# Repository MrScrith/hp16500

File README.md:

# hp16500
Project contains multiple items for the hp16500 testing mainframe.

Eventually there will be scripts, configurations, interface board designs and more as I get my HP16500 up and running and integrated into my FPGA and Embedded development workflow.

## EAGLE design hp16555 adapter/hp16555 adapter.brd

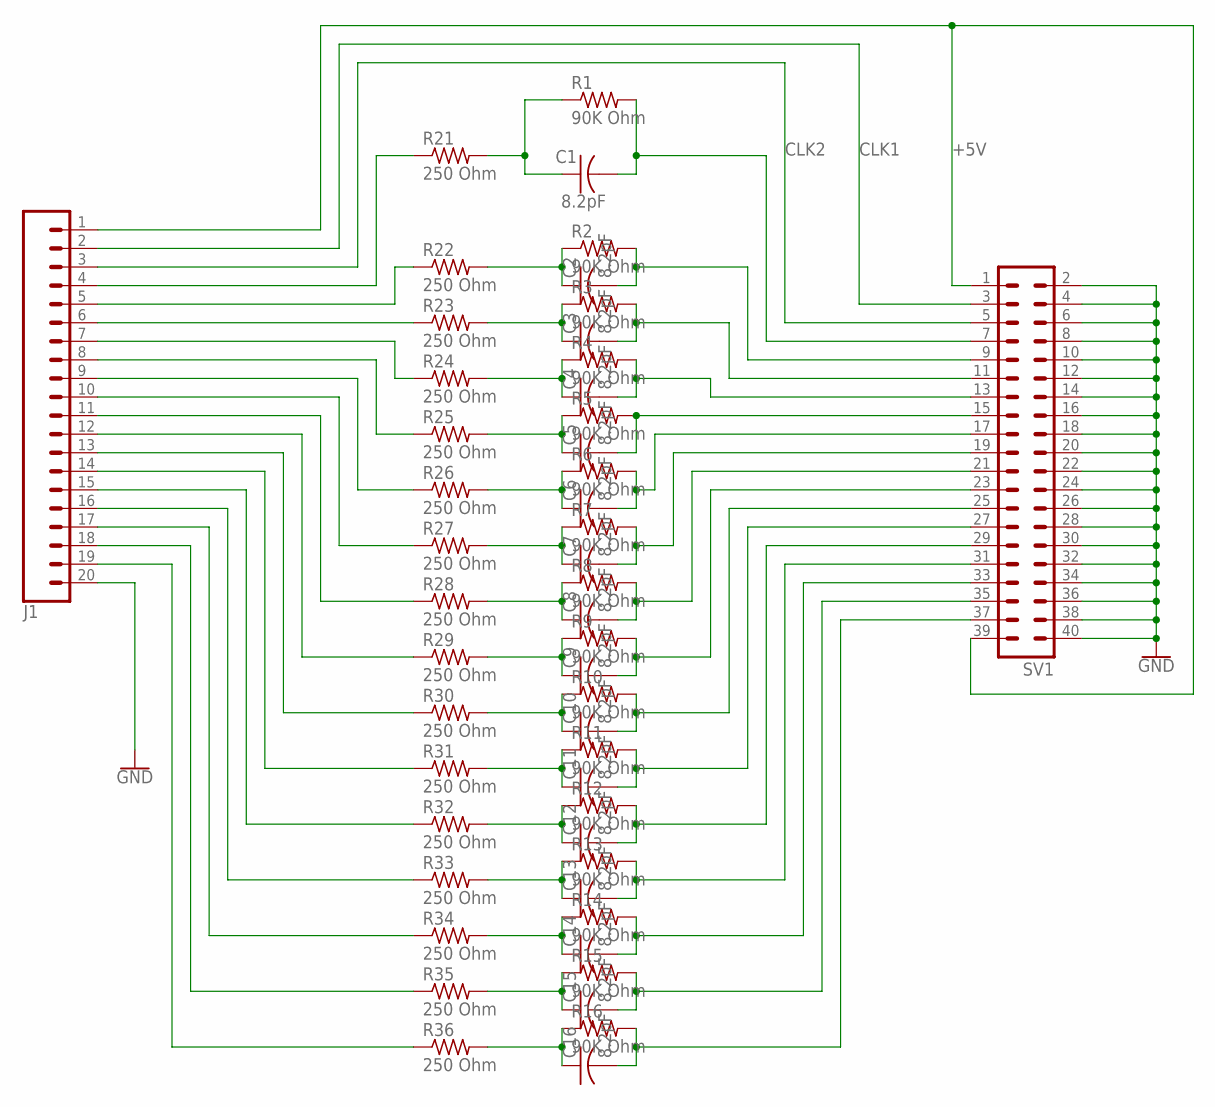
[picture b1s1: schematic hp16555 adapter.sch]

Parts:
C1, C2, C3, C4, C5, C6, C7, C8, C9, C10, C11, C12, C13, C14, C15, C16: 8.2pF; C1206
J1: CONN_20; 1X20
R1, R2, R3, R4, R5, R6, R7, R8, R9, R10, R11, R12, R13, R14, R15, R16: 90K Ohm; M1206
R21, R22, R23, R24, R25, R26, R27, R28, R29, R30, R31, R32, R33, R34, R35, R36: 250 Ohm; M1206
SV1: MA20-2

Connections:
+5V: J1.1, SV1.1, SV1.39
CLK1: J1.2, SV1.3
CLK2: J1.3, SV1.5
D0: C16.2, R16.2, SV1.37
D0-I: J1.19, R36.1
D1: C15.2, R15.2, SV1.35
D1-I: J1.18, R35.1
D2: C14.2, R14.2, SV1.33
D2-I: J1.17, R34.1
D3: C13.2, R13.2, SV1.31
D3-I: J1.16, R33.1
D4: C12.2, R12.2, SV1.29
D4-I: J1.15, R32.1
D5: C11.2, R11.2, SV1.27
D5-I: J1.14, R31.1
D6: C10.2, R10.2, SV1.25
D6-I: J1.13, R30.1
D7: C9.2, R9.2, SV1.23
D7-I: J1.12, R29.1
D8: C8.2, R8.2, SV1.21
D8-I: J1.11, R28.1
D9: C7.2, R7.2, SV1.19
D9-I: J1.10, R27.1
D10: C6.2, R6.2, SV1.17
D10-I: J1.9, R26.1
D11: C5.2, R5.2, SV1.15
D11-I: J1.8, R25.1
D12: C4.2, R4.2, SV1.13
D12-I: J1.7, R24.1
D13: C3.2, R3.2, SV1.11
D13-I: J1.6, R23.1
D14: C2.2, R2.2, SV1.9
D14-I: J1.5, R22.1
D15: C1.2, R1.2, SV1.7
D15-I: J1.4, R21.1
GND: J1.20, SV1.2, SV1.4, SV1.6, SV1.8, SV1.10, SV1.12, SV1.14, SV1.16, SV1.18, SV1.20, SV1.22, SV1.24, SV1.26, SV1.28, SV1.30, SV1.32, SV1.34, SV1.36, SV1.38, SV1.40
unnamed: C16.1, R16.1, R36.2
unnamed: C15.1, R15.1, R35.2
unnamed: C14.1, R14.1, R34.2
unnamed: C13.1, R13.1, R33.2
unnamed: C12.1, R12.1, R32.2
unnamed: C11.1, R11.1, R31.2
unnamed: C10.1, R10.1, R30.2
unnamed: C9.1, R9.1, R29.2
unnamed: C8.1, R8.1, R28.2
unnamed: C7.1, R7.1, R27.2
unnamed: C6.1, R6.1, R26.2
unnamed: C5.1, R5.1, R25.2
unnamed: C4.1, R4.1, R24.2
unnamed: C3.1, R3.1, R23.2
unnamed: C2.1, R2.1, R22.2
unnamed: C1.1, R1.1, R21.2

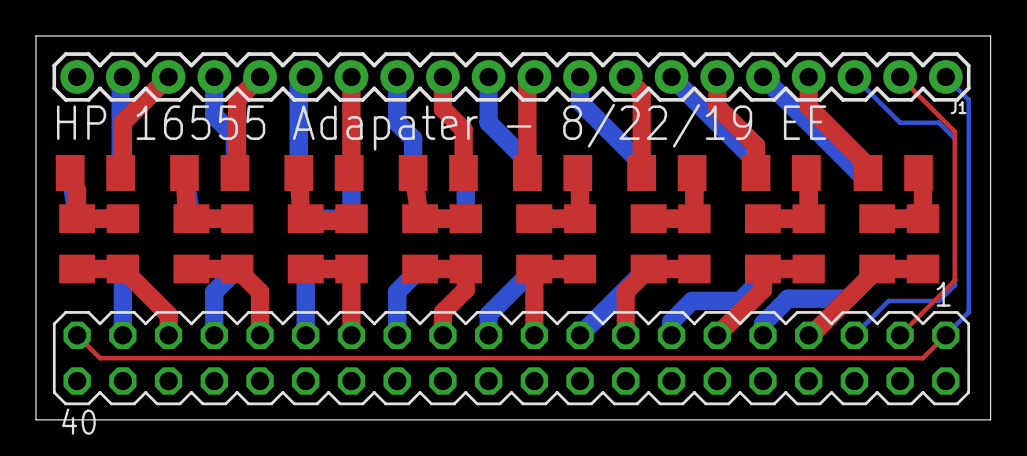
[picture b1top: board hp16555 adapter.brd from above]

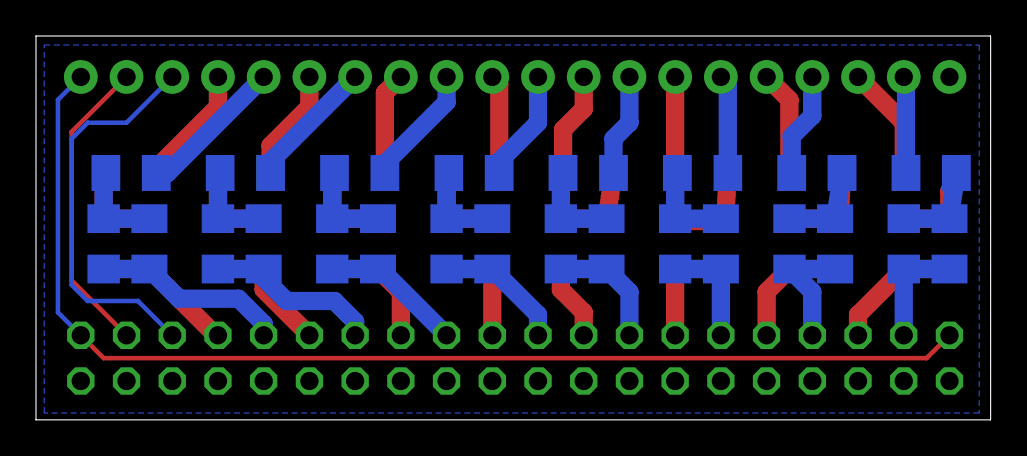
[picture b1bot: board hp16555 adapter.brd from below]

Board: 2 copper layers, 53.0 x 21.3 mm, 50 parts (24 on the bottom side), 52 nets.

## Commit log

2019-08-22 Updated readme with project info
2019-08-22 Adding the 0.1 version of the board, initial development, lots of work left to do.
2019-08-22 Cleaned up design, made it more compact, entered values into schematic

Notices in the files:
parts and their libraries:
SparkFun-Connectors: Licensing: Creative Commons ShareAlike 4.0 International - https://creativecommons.org/licenses/by-sa/4.0
